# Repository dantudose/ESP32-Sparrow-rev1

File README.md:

# ESP32-Sparrow-rev1

The ESP32 Sparrow is a development board supporting the ESP32-WROVER module. It is fully Arduino-compatible and it comes with two on-board environmental sensors (Bosch temperature, humidity, pressure and air quality BME680 and Lite-On luxmeter LTR308), an RGB LED, expansion headers, a Li-Po charger circuit and a 18650 battery holder and a USB programming interface.

Repository Contents
-------------------

* **/Hardware** - Eagle design files (.brd, .sch)

Documentation
--------------
* **[Hookup Guide](https://ocw.cs.pub.ro/courses/iothings/laboratoare/2022/lab1)** - Basic hookup tutorial for ESP32 Sparrow

License Information
-------------------

This product is _**open source**_! 

Please review the LICENSE file for license information. 

Distributed as-is; no warranty is given.

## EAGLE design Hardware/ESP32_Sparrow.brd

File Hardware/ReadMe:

ESP32 Sparrow rev1 Eagle CAD files

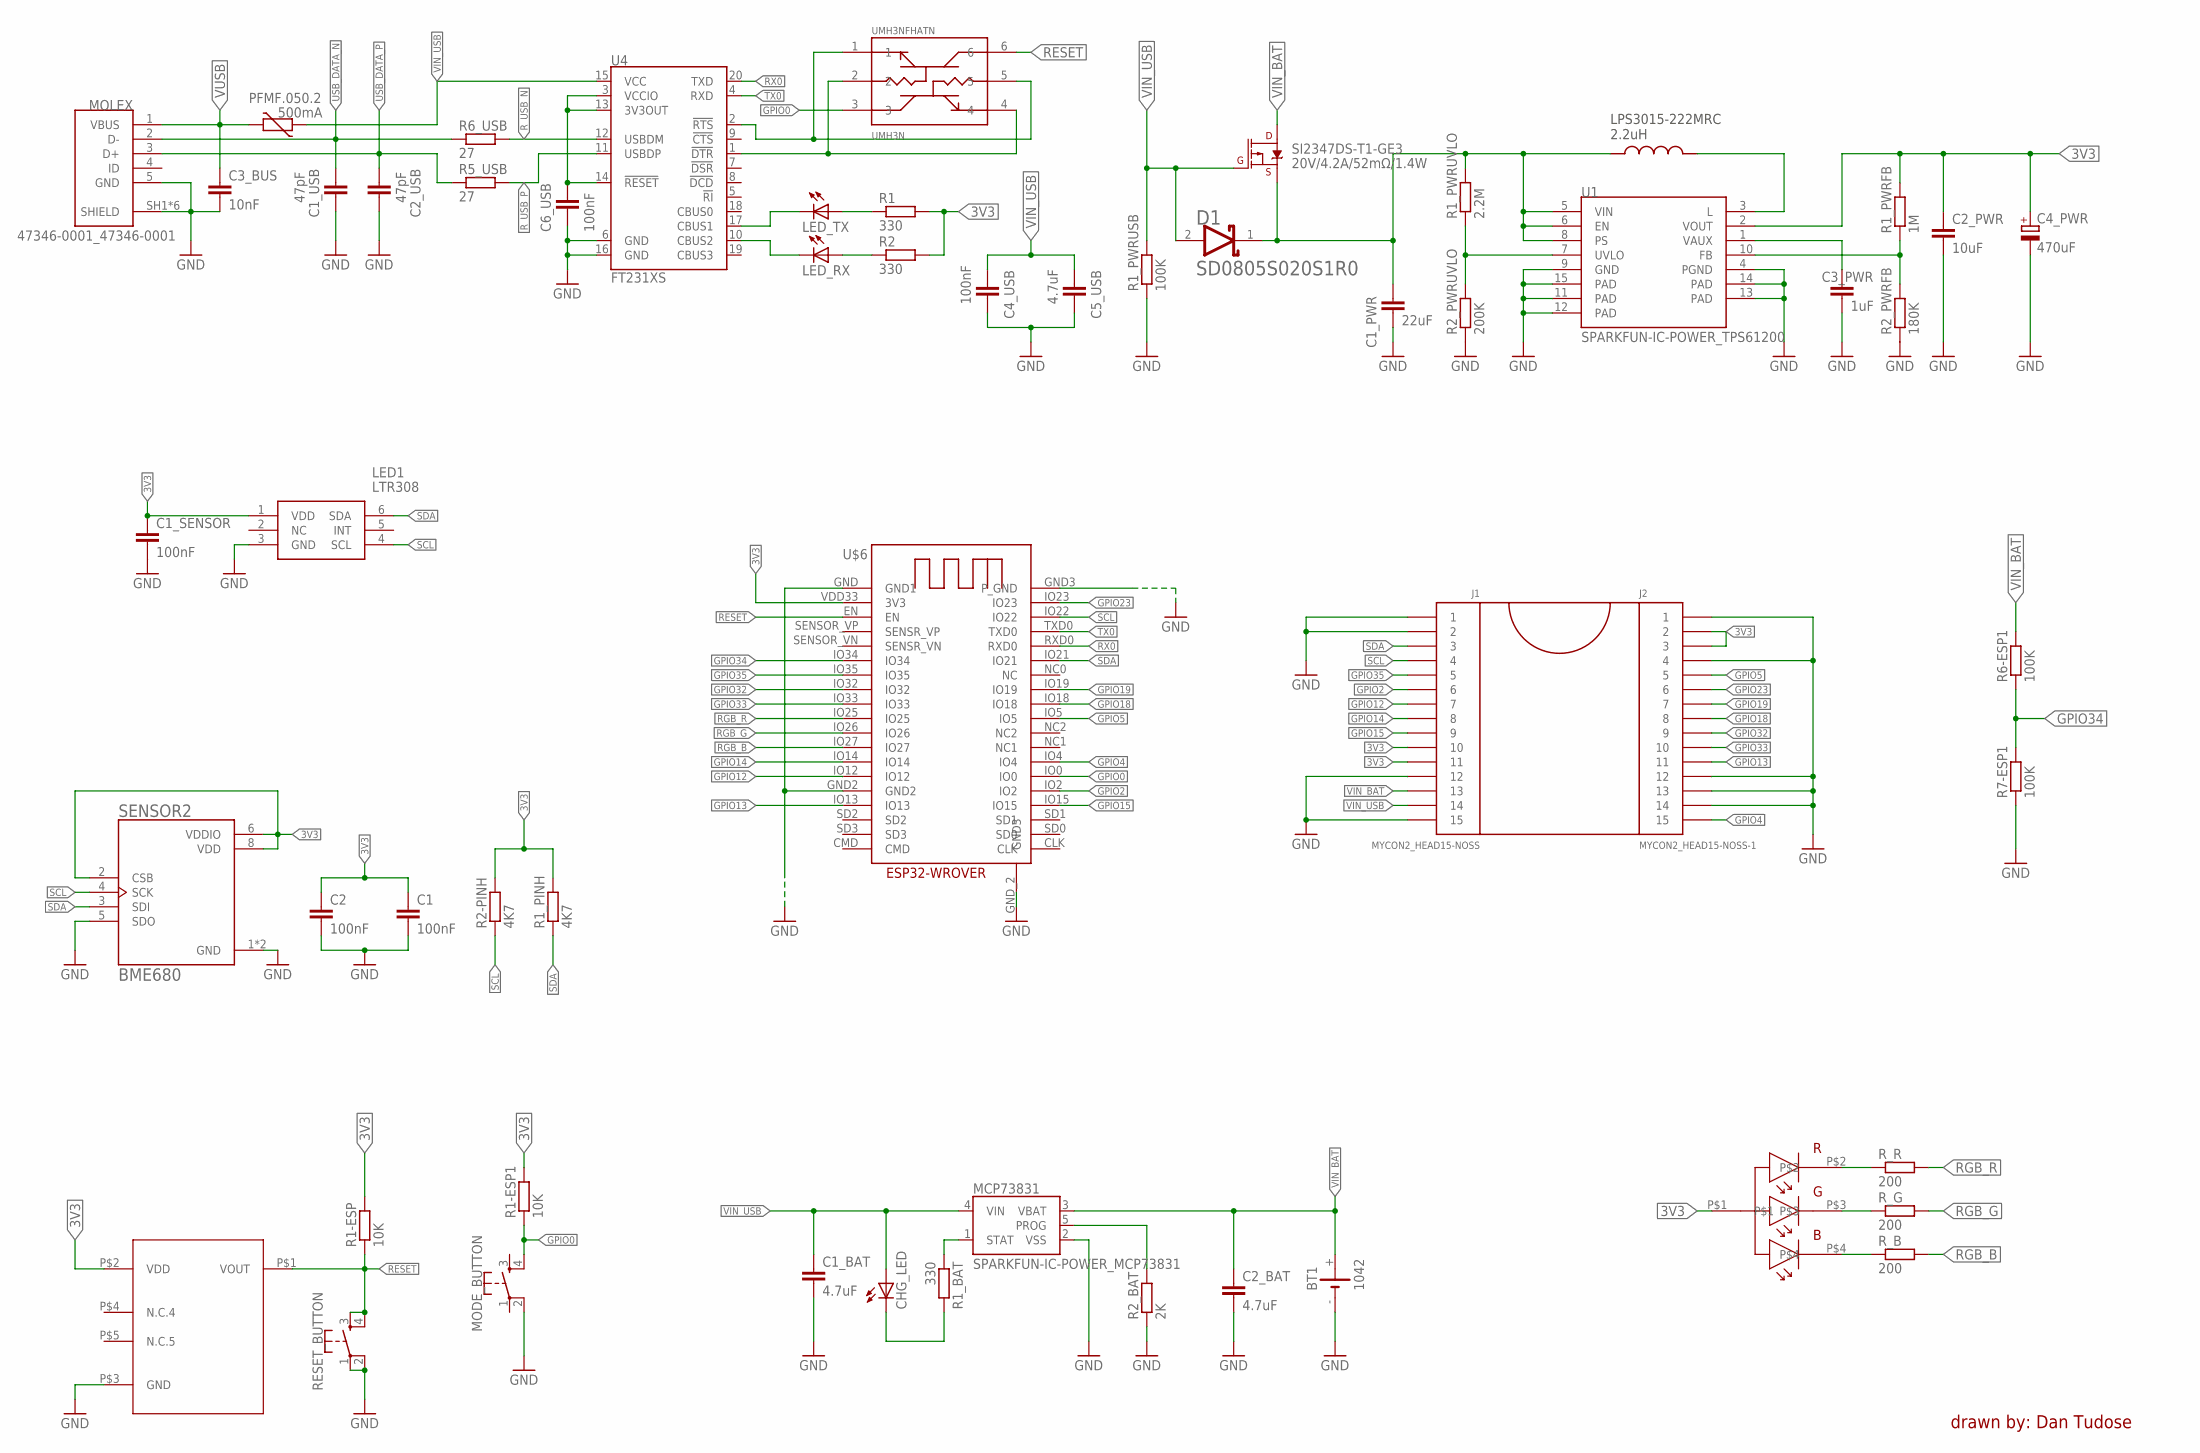
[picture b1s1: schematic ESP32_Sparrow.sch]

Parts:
BD48E27G-TR: BD48E27G-TR_BD48E27G-TR; BD48E27G-TR_SSOP5
BT1: 1042; BAT_1042
C1, C2: 100nF; EAGLE-LTSPICE_C0402
C1_BAT, C2_BAT, C5_USB: 4.7uF; RCL_C0603
C1_PWR: 22uF; RCL_C0603
C1_SENSOR, C4_USB, C6_USB: 100nF; RCL_C0603
C1_USB, C2_USB: 47pF; RCL_C0603
C2_PWR: 10uF; RCL_C0603
C3_BUS: 10nF; RCL_C0603
C3_PWR: 1uF; RCL_C0603
C4_PWR: 470uF; RCL_D/7343-31R
CHG_LED: ADAFRUIT_LEDCHIP-LED0603; ADAFRUIT_CHIP-LED0603
D1: AVX---SD0805S020S1R0_AVX_SD0805S020S1R0AVX_SD0805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; AVX---SD0805S020S1R0_AVX_SD0805S020S1R0_0
J1: MYCON2_HEAD15-NOSS
J2: MYCON2_HEAD15-NOSS-1
LED1: LTR308; SAMACSYS_PARTS_LTR303ALS01
LED_RX: ADAFRUIT_LEDCHIP-LED0603; ADAFRUIT_CHIP-LED0603
LED_TX: ADAFRUIT_LEDCHIP-LED0603; ADAFRUIT_CHIP-LED0603
MCP73831: SPARKFUN-IC-POWER_MCP73831; SPARKFUN-IC-POWER_SOT23-5
MODE_BUTTON: SPARKFUN-SWITCHES_MOMENTARY-SWITCH-SPST-2-SMD-4.6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; SPARKFUN-SWITCHES_TACTILE_SWITCH_SMD_4.6X2.8MM
MOLEX: 47346-0001_47346-0001; 47346-0001_MOLEX_47346-0001
PFMF.050.2: 500mA; VARISTOR_CT/CN1812
R1, R1_BAT, R2: 330; EAGLE-LTSPICE_R0402
R1-ESP, R1-ESP1: 10K; EAGLE-LTSPICE_R0402
R1_PINH, R2-PINH: 4K7; EAGLE-LTSPICE_R0402
R1_PWRFB: 1M; EAGLE-LTSPICE_R0402
R1_PWRUSB, R6-ESP1, R7-ESP1: 100K; EAGLE-LTSPICE_R0402
R1_PWRUVLO: 2.2M; EAGLE-LTSPICE_R0402
R2_BAT: 2K; EAGLE-LTSPICE_R0402
R2_PWRFB: 180K; EAGLE-LTSPICE_R0402
R2_PWRUVLO: 200K; EAGLE-LTSPICE_R0402
R5_USB, R6_USB: 27; EAGLE-LTSPICE_R0402
RESET_BUTTON: SPARKFUN-SWITCHES_MOMENTARY-SWITCH-SPST-2-SMD-4.6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; SPARKFUN-SWITCHES_TACTILE_SWITCH_SMD_4.6X2.8MM
R_B: 200; EAGLE-LTSPICE_R0402
R_G: 200; EAGLE-LTSPICE_R0402
R_R: 200; EAGLE-LTSPICE_R0402
SENSOR2: BME680; BME680_PSON80P300X300X100-8N
SI2347DS-T1-GE3: 20V/4.2A/52mΩ/1.4W; SPARKFUN-DISCRETESEMI_SOT23-3
U1: SPARKFUN-IC-POWER_TPS61200; SPARKFUN-IC-POWER_QFN-10_PAD
U4: FT231XS; SPARKFUN-IC-COMMS_SSOP20_L
U$2: 150202M153130_150202M153130-RGB; 150202M153130_150202M153130
U$5: LPS3015_LPS3015; LPS3015_LPS3015-222MRC
U$6: ESP32-WROVER_ESP32-WROVER
UMH3NFHATN: UMH3N_UMH3N; UMH3N_SOP65P210X100-6N

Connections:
3V3: BD48E27G-TR.P$2 (VDD), C1.1, C1_SENSOR.1, C2.1, C2_PWR.1, C4_PWR.+, J1.10, J1.11, J2.2, J2.3, LED1.1 (VDD), R1.2, R1-ESP.2, R1-ESP1.2, R1_PINH.2, R1_PWRFB.2, R2.2, R2-PINH.2, SENSOR2.2 (CSB), SENSOR2.6 (VDDIO), SENSOR2.8 (VDD), U1.2 (VOUT), U$2.P$1, U$6.VDD33 (3V3)
GND: BD48E27G-TR.P$3 (GND), BT1.-, C1.2, C1_BAT.2, C1_PWR.2, C1_SENSOR.2, C1_USB.2, C2.2, C2_BAT.2, C2_PWR.2, C2_USB.2, C3_BUS.2, C3_PWR.2, C4_PWR.-, C4_USB.2, C5_USB.2, C6_USB.2, J1.1, J1.2, J1.12, J1.15, J2.1, J2.4, J2.12, J2.13, J2.14, LED1.3 (GND), MCP73831.2 (VSS), MODE_BUTTON.2, MOLEX.5 (GND), MOLEX.SH1 (SHIELD), MOLEX.SH2 (SHIELD), MOLEX.SH3 (SHIELD), MOLEX.SH4 (SHIELD), MOLEX.SH5 (SHIELD), MOLEX.SH6 (SHIELD), R1_PWRUSB.1, R2_BAT.1, R2_PWRFB.1, R2_PWRUVLO.1, R7-ESP1.1, RESET_BUTTON.1, RESET_BUTTON.2, SENSOR2.1 (GND), SENSOR2.5 (SDO), SENSOR2.7 (GND), U1.4 (PGND), U1.9 (GND), U1.11 (PAD), U1.12 (PAD), U1.13 (PAD), U1.14 (PAD), U1.15 (PAD), U4.6 (GND), U4.16 (GND), U$6.GND (GND1), U$6.GND2, U$6.GND3 (P_GND), U$6.GND_2 (GND3)
GPIO0: MODE_BUTTON.4, R1-ESP1.1, U$6.IO0, UMH3NFHATN.3
GPIO2: J1.6, U$6.IO2
GPIO4: J2.15, U$6.IO4
GPIO5: J2.5, U$6.IO5
GPIO12: J1.7, U$6.IO12
GPIO13: J2.11, U$6.IO13
GPIO14: J1.8, U$6.IO14
GPIO15: J1.9, U$6.IO15
GPIO18: J2.8, U$6.IO18
GPIO19: J2.7, U$6.IO19
GPIO23: J2.6, U$6.IO23
GPIO32: J2.9, U$6.IO32
GPIO33: J2.10, U$6.IO33
GPIO34: R6-ESP1.1, R7-ESP1.2, U$6.IO34
GPIO35: J1.5, U$6.IO35
unnamed: R1_PWRUVLO.1, R2_PWRUVLO.2, U1.7 (UVLO)
unnamed: MCP73831.1 (STAT), R1_BAT.1
unnamed: CHG_LED.C, R1_BAT.2
unnamed: MCP73831.5 (PROG), R2_BAT.2
unnamed: R_R.1, U$2.P$2
unnamed: U1.3 (L), U$5.P$2
unnamed: R_G.1, U$2.P$3
unnamed: R_B.1, U$2.P$4
unnamed: R1_PWRFB.1, R2_PWRFB.2, U1.10 (FB)
unnamed: C3_PWR.1, U1.1 (VAUX)
unnamed: C6_USB.1, U4.3 (VCCIO), U4.13 (3V3OUT), U4.14 (!RESET)
unnamed: LED_TX.A, R1.1
unnamed: LED_RX.A, R2.1
unnamed: U4.1 (!DTR), UMH3NFHATN.2, UMH3NFHATN.4
unnamed: LED_TX.C, U4.17 (CBUS1)
unnamed: LED_RX.C, U4.10 (CBUS2)
unnamed: U4.2 (!RTS), UMH3NFHATN.1, UMH3NFHATN.5
RESET: BD48E27G-TR.P$1 (VOUT), R1-ESP.1, RESET_BUTTON.3, RESET_BUTTON.4, U$6.EN, UMH3NFHATN.6
RGB_B: R_B.2, U$6.IO27
RGB_G: R_G.2, U$6.IO26
RGB_R: R_R.2, U$6.IO25
RX0: U4.20 (TXD), U$6.RXD0
R_USB_N: R6_USB.2, U4.12 (USBDM)
R_USB_P: R5_USB.2, U4.11 (USBDP)
SCL: J1.4, LED1.4 (SCL), R2-PINH.1, SENSOR2.4 (SCK), U$6.IO22
SDA: J1.3, LED1.6 (SDA), R1_PINH.1, SENSOR2.3 (SDI), U$6.IO21
TX0: U4.4 (RXD), U$6.TXD0
USB_DATA_N: C1_USB.1, MOLEX.2 (D-), R6_USB.1
USB_DATA_P: C2_USB.1, MOLEX.3 (D+), R5_USB.1
VIN: C1_PWR.1, D1.1 (CATHODE), R1_PWRUVLO.2, SI2347DS-T1-GE3.2 (S), U1.5 (VIN), U1.6 (EN), U1.8 (PS), U$5.P$1
VIN_BAT: BT1.+, C2_BAT.1, J1.13, MCP73831.3 (VBAT), R6-ESP1.2, SI2347DS-T1-GE3.3 (D)
VIN_USB: C1_BAT.1, C4_USB.1, C5_USB.1, CHG_LED.A, D1.2 (ANODE), J1.14, MCP73831.4 (VIN), PFMF.050.2.1, R1_PWRUSB.2, SI2347DS-T1-GE3.1 (G), U4.15 (VCC)
VUSB: C3_BUS.1, MOLEX.1 (VBUS), PFMF.050.2.2

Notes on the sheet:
drawn by: Dan Tudose

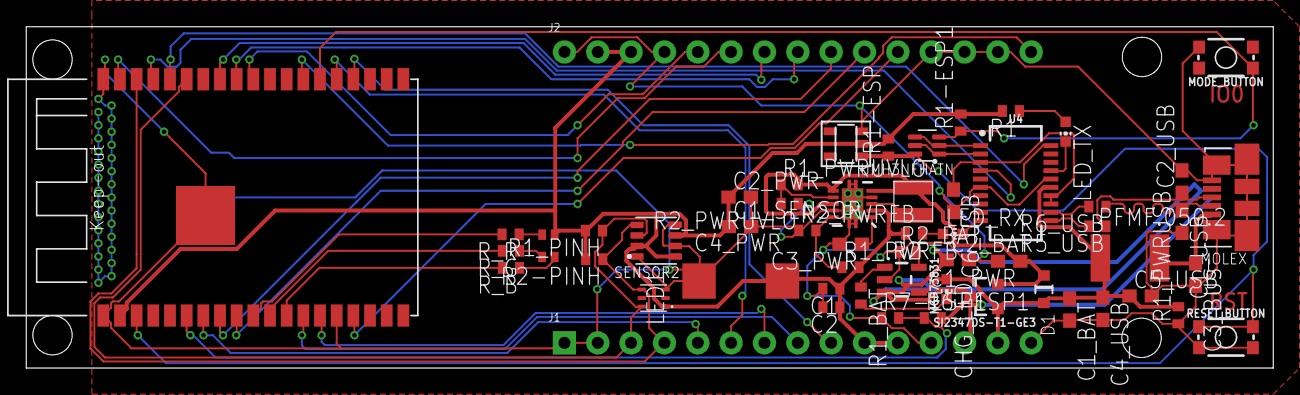
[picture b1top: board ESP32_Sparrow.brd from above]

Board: 2 copper layers, 95.0 x 26.0 mm, 57 parts (1 on the bottom side), 50 nets.
